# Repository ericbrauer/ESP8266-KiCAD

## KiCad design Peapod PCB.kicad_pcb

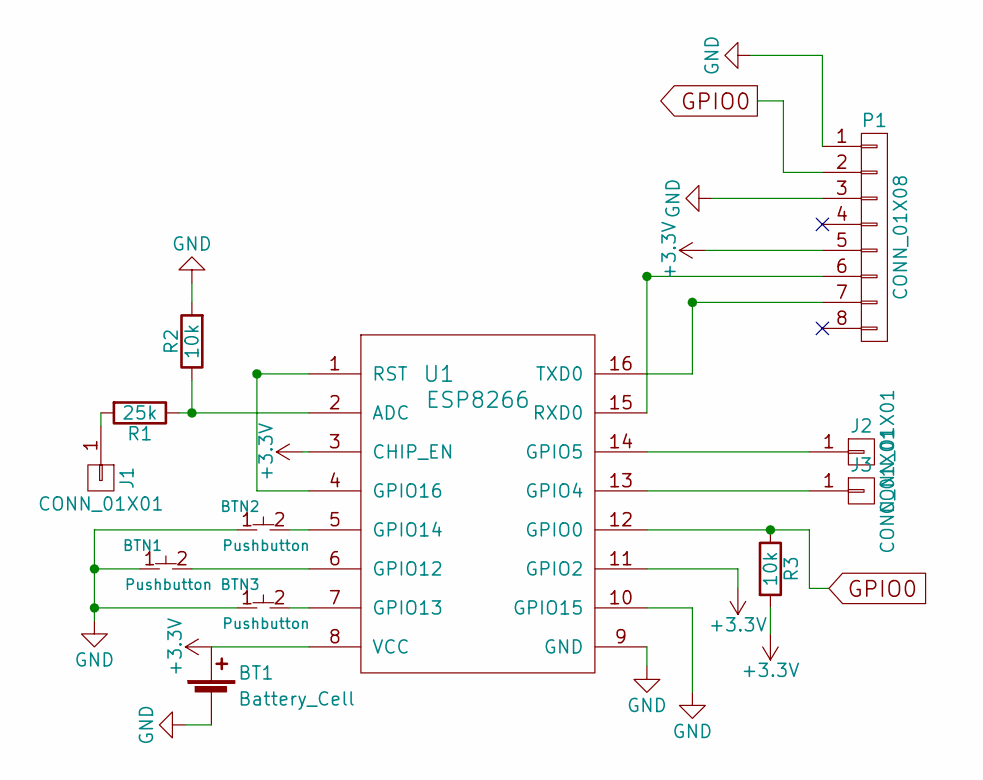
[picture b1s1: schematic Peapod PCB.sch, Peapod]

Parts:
BT1: Battery_Cell; JST_PH_B2B-PH-K_02x2.00mm_Straight; Manufacture Part B2B-PH-K-S(LF)(SN)
BTN1, BTN2, BTN3: Pushbutton
J1, J2, J3: CONN_01X01; Alligator Pad
P1: CONN_01X08; Pin_Header_Straight_1x08_Pitch2.54mm
R1: 25k; R_0805_HandSoldering
R2, R3: 10k; R_0805_HandSoldering
U1: ESP8266; ESP-12E_SMD

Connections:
+3V3: BT1.1 (+), P1.5, R3.2, U1.3 (CHIP_EN), U1.8 (VCC), U1.11 (GPIO2); also elsewhere on the board
GND: BT1.2 (-), BTN1.1, BTN2.1, BTN3.1, P1.1, P1.3, R2.2, U1.9 (GND), U1.10 (GPIO15); also elsewhere on the board
GPIO0: P1.2, R3.1, U1.12 (GPIO0); also elsewhere on the board
unnamed: BTN1.2, U1.6 (GPIO12)
unnamed: BTN2.2, U1.5 (GPIO14)
unnamed: BTN3.2, U1.7 (GPIO13)
unnamed: J1.1, R1.2
unnamed: J2.1, U1.14 (GPIO5)
unnamed: J3.1, U1.13 (GPIO4)
unnamed 10: P1.6, U1.15 (RXD0); also elsewhere on the board
unnamed 11: P1.7, U1.16 (TXD0); also elsewhere on the board
unnamed: R1.1, R2.1, U1.2 (ADC)
unnamed: U1.1 (RST), U1.4 (GPIO16)

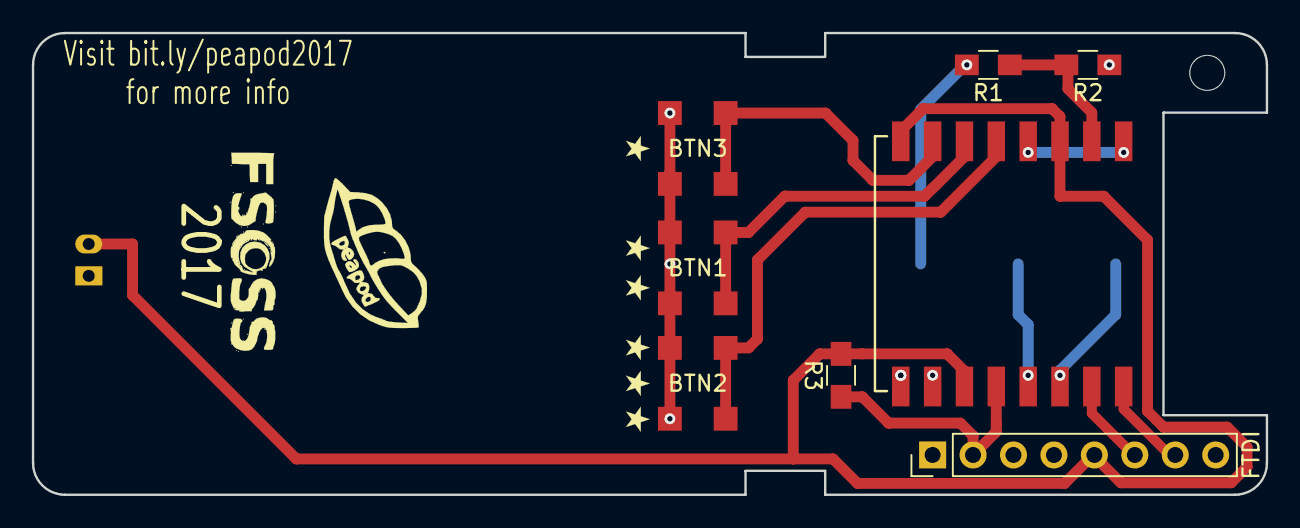
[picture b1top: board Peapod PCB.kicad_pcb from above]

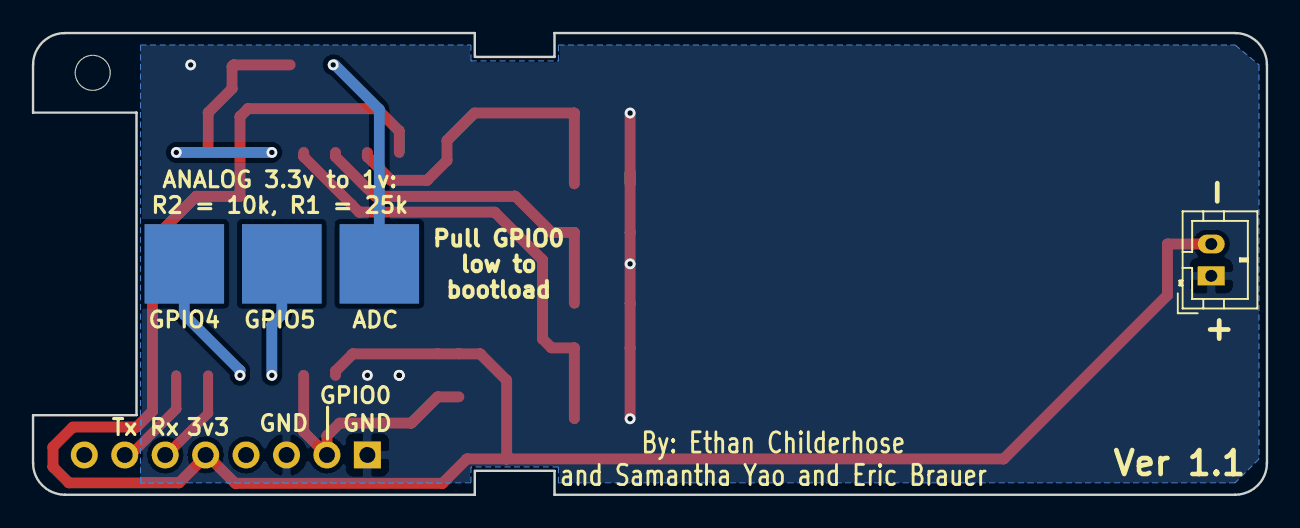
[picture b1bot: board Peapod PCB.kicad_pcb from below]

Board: 2 copper layers, 77.5 x 29.0 mm, 12 parts (4 on the bottom side), 13 nets.

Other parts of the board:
FTDI: CONN_01X08; Pin_Header_Straight_1x08_Pitch2.54mm

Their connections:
+3V3: FTDI.5; also elsewhere on the board
GND: FTDI.1, FTDI.3; also elsewhere on the board
GPIO0: FTDI.2; also elsewhere on the board
unnamed 10: FTDI.6; also elsewhere on the board
unnamed 11: FTDI.7; also elsewhere on the board

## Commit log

2017-09-14 initial plan for the outline of new peapod
2017-09-14 new peapod with routing complete
2017-09-14 routing done, silkscreen in progress
2017-09-14 fixed a problem with previous shape
2017-09-14 silkscreening done. Pending approval.
2017-09-14 added BOM file
2017-09-14 added gerbers/
2017-09-16 making revisions to design
2017-09-16 final touches on peapod. Feature complete.
2017-09-16 added a keychain(?) hole, created gerbers and BOM file.
2017-09-16 forgot to ctrl+s
2017-09-16 reversed pins on battery JST to reflect most common pinout
2017-09-16 updated gerber files
